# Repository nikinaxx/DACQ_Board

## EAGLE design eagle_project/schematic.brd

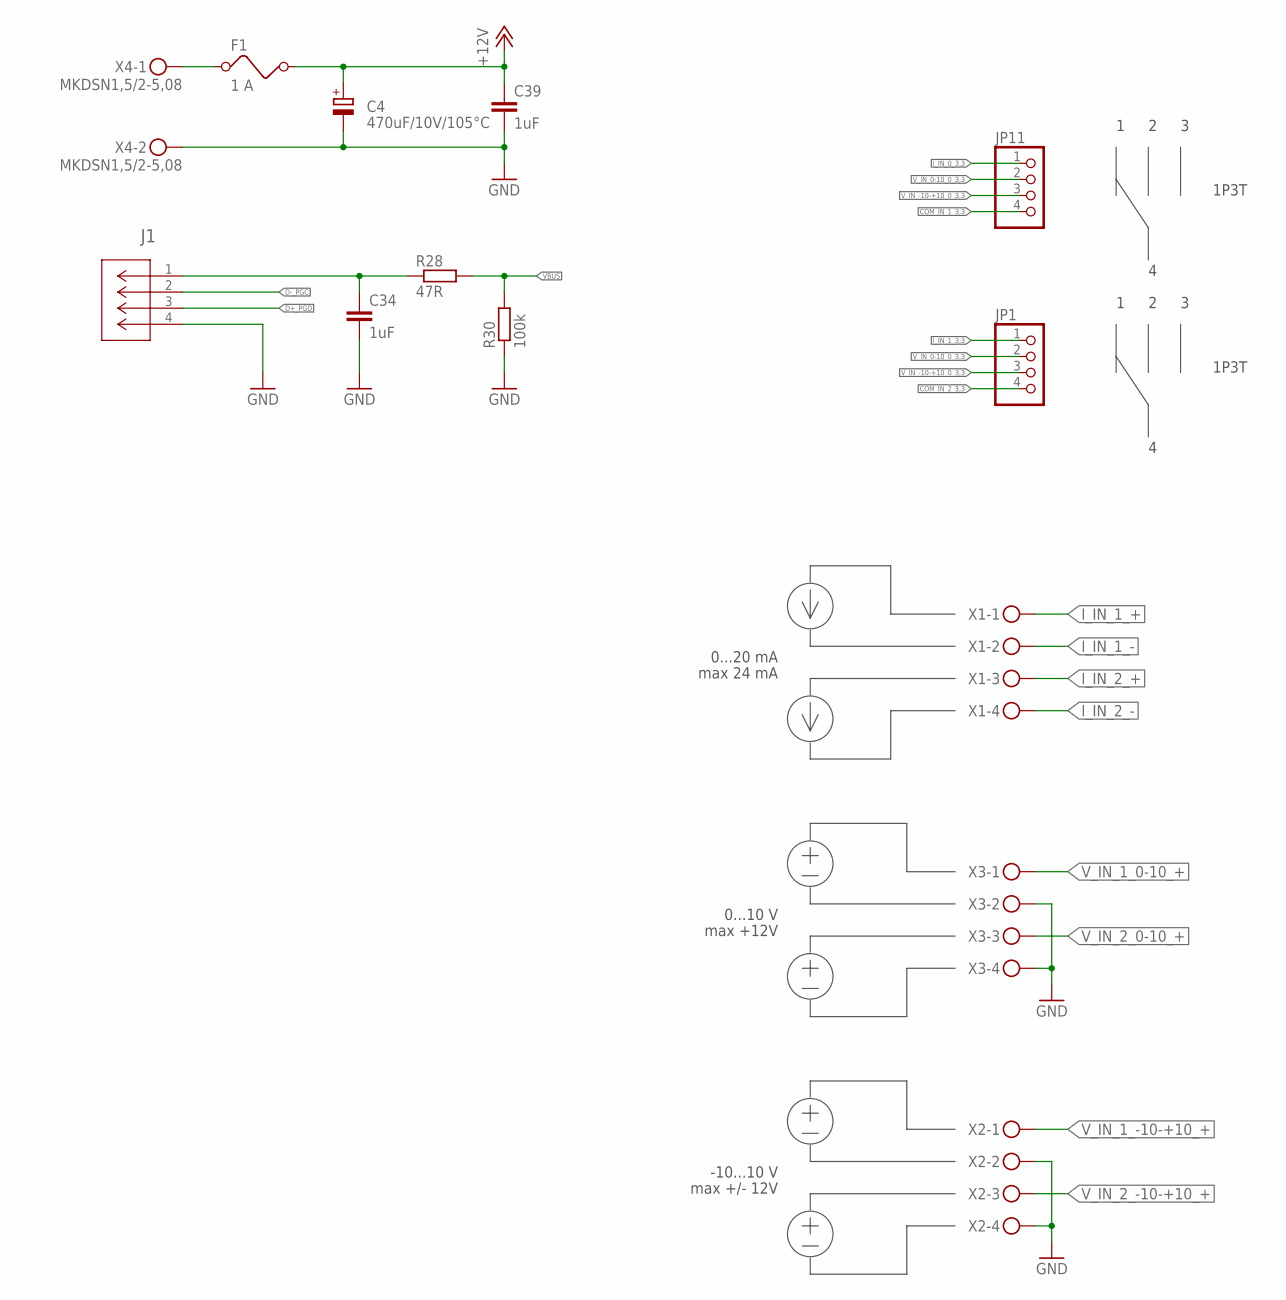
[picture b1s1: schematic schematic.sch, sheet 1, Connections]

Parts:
C4: 470uF/10V/105°C; E3,5-8
C34, C39: 1uF; C0805
F1: 1 A; FUSE
J1: USB-B; CONN_67068-8000_MOL
JP1, JP11: PINHD-1X4; 1X04
R28: 47R; M0805
R30: 100k; M0805
X1, X2, X3: MKDSN1,5/4-5,08
X4: MKDSN1,5/2-5,08

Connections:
+12V: C4.+, C39.1, F1.2; also elsewhere on the board
COM_IN_1_3,3: JP11.4
COM_IN_2_3,3: JP1.4
D+_PGD: J1.3; also elsewhere on the board
D-_PGC: J1.2; also elsewhere on the board
GND: C4.-, C34.2, C39.2, J1.4, R30.1, X2.2, X2.4, X3.2, X3.4, X4.2; also elsewhere on the board
I_IN_0_3,3: JP11.1; also elsewhere on the board
I_IN_1_3,3: JP1.1; also elsewhere on the board
I_IN_1_+: X1.1; also elsewhere on the board
I_IN_1_-: X1.2
I_IN_2_+: X1.3; also elsewhere on the board
I_IN_2_-: X1.4
unnamed: C34.1, J1.1, R28.1
unnamed: F1.1, X4.1
VBUS: R28.2, R30.2; also elsewhere on the board
V_IN_0-10_0_3,3: JP1.2, JP11.2; also elsewhere on the board
V_IN_1_0-10_+: X3.1; also elsewhere on the board
V_IN_1_-10-+10_+: X2.1; also elsewhere on the board
V_IN_2_0-10_+: X3.3; also elsewhere on the board
V_IN_2_-10-+10_+: X2.3; also elsewhere on the board
V_IN_-10-+10_0_3,3: JP1.3, JP11.3; also elsewhere on the board

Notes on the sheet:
max +12V
0...10 V
max 24 mA
0...20 mA
1P3T
max +/- 12V
-10...10 V

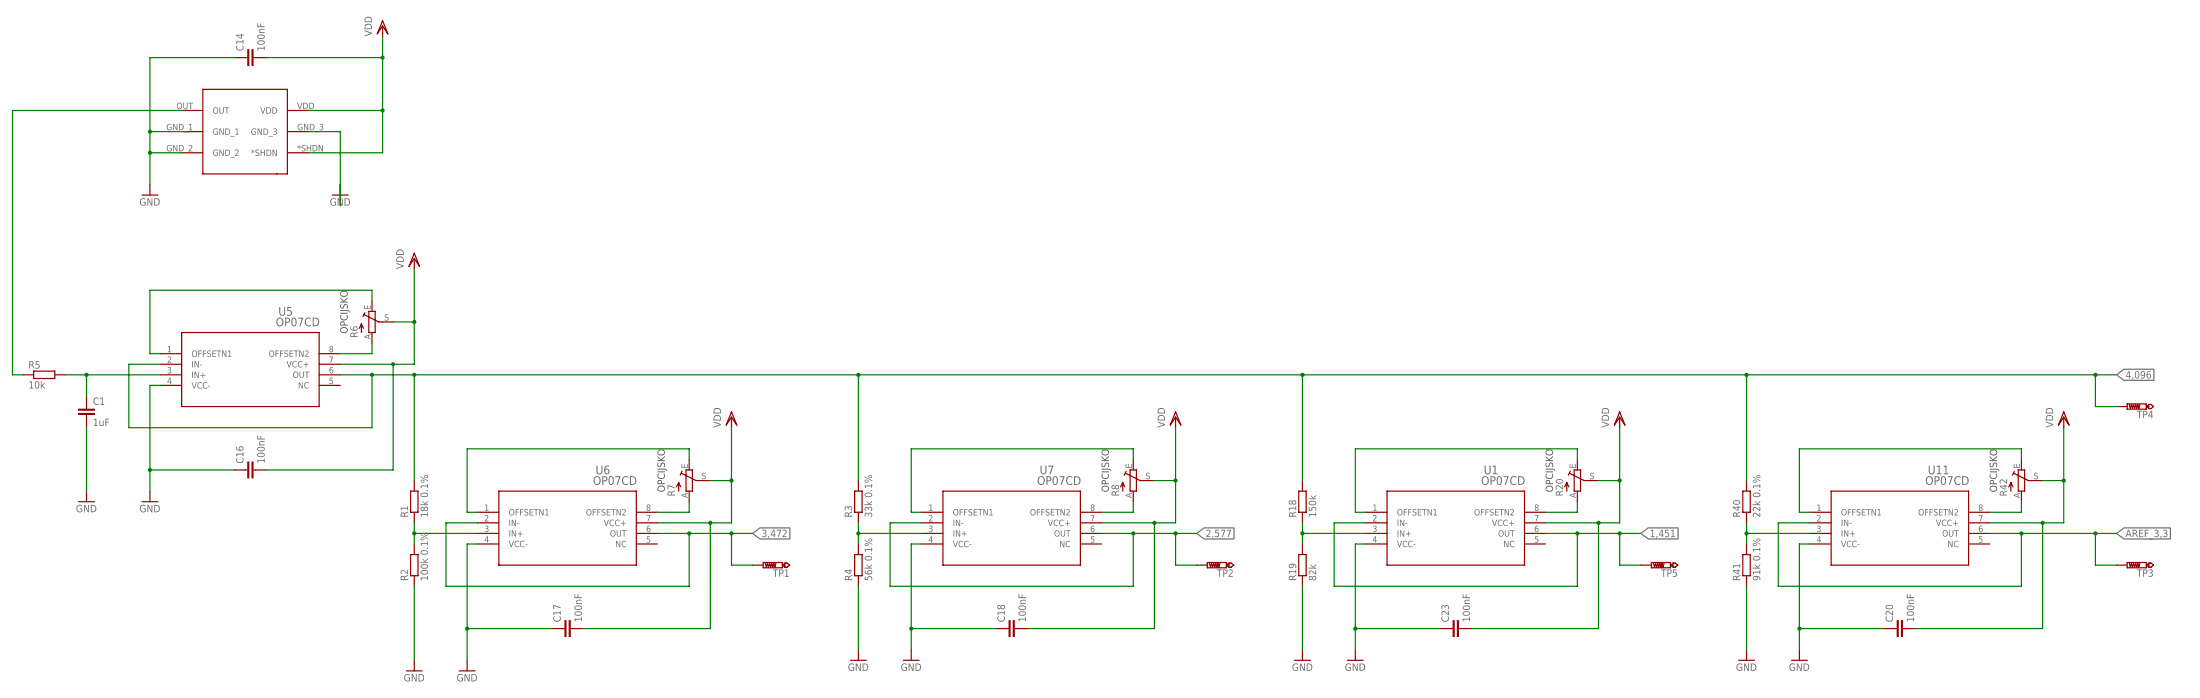
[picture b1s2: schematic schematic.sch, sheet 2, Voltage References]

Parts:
C1: 1uF; C0805
C14, C16, C17, C18, C20, C23: 100nF; C0805
R1: 18k 0.1%; R0805
R2: 100k 0.1%; R0805
R3: 33k 0.1%; R0805
R4: 56k 0.1%; R0805
R5: 10k; R0805
R6, R7, R8, R20, R42: TRIM_EU-S64W; S64W
R18: 150k; R0805
R19: 82k; R0805
R40: 22k 0.1%; R0805
R41: 91k 0.1%; R0805
TP1, TP2, TP3, TP4, TP5: PTR1PAD1-13; P1-13
U1, U5, U6, U7, U11: OP07CD; D8
U4: MCP1501T-40E/CHY; SOT26

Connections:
1,451: TP5.TP, U1.2 (IN-), U1.6 (OUT); also elsewhere on the board
2,577: TP2.TP, U7.2 (IN-), U7.6 (OUT); also elsewhere on the board
3,472: TP1.TP, U6.2 (IN-), U6.6 (OUT); also elsewhere on the board
4,096: R1.2, R3.2, R18.2, R40.2, TP4.TP, U5.2 (IN-), U5.6 (OUT); also elsewhere on the board
AREF_3,3: TP3.TP, U11.2 (IN-), U11.6 (OUT); also elsewhere on the board
GND: C1.2, C14.1, C16.1, C17.1, C18.1, C20.1, C23.1, R2.1, R4.1, R19.1, R41.1, U1.4 (VCC-), U4.GND_1, U4.GND_2, U4.GND_3, U5.4 (VCC-), U6.4 (VCC-), U7.4 (VCC-), U11.4 (VCC-); also elsewhere on the board
unnamed: R3.1, R4.2, U7.3 (IN+)
unnamed: R6.A, U5.8 (OFFSETN2)
unnamed: C1.1, R5.2, U5.3 (IN+)
unnamed: R6.E, U5.1 (OFFSETN1)
unnamed: R5.1, U4.OUT
unnamed: R1.1, R2.2, U6.3 (IN+)
unnamed: R7.A, U6.8 (OFFSETN2)
unnamed: R7.E, U6.1 (OFFSETN1)
unnamed: R8.A, U7.8 (OFFSETN2)
unnamed: R8.E, U7.1 (OFFSETN1)
unnamed: R18.1, R19.2, U1.3 (IN+)
unnamed: R20.A, U1.8 (OFFSETN2)
unnamed: R20.E, U1.1 (OFFSETN1)
unnamed: R40.1, R41.2, U11.3 (IN+)
unnamed: R42.A, U11.8 (OFFSETN2)
unnamed: R42.E, U11.1 (OFFSETN1)
VDD: C14.2, C16.2, C17.2, C18.2, C20.2, C23.2, R6.S, R7.S, R8.S, R20.S, R42.S, U1.7 (VCC+), U4.*SHDN, U4.VDD, U5.7 (VCC+), U6.7 (VCC+), U7.7 (VCC+), U11.7 (VCC+); also elsewhere on the board

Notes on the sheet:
OPCIJSKO

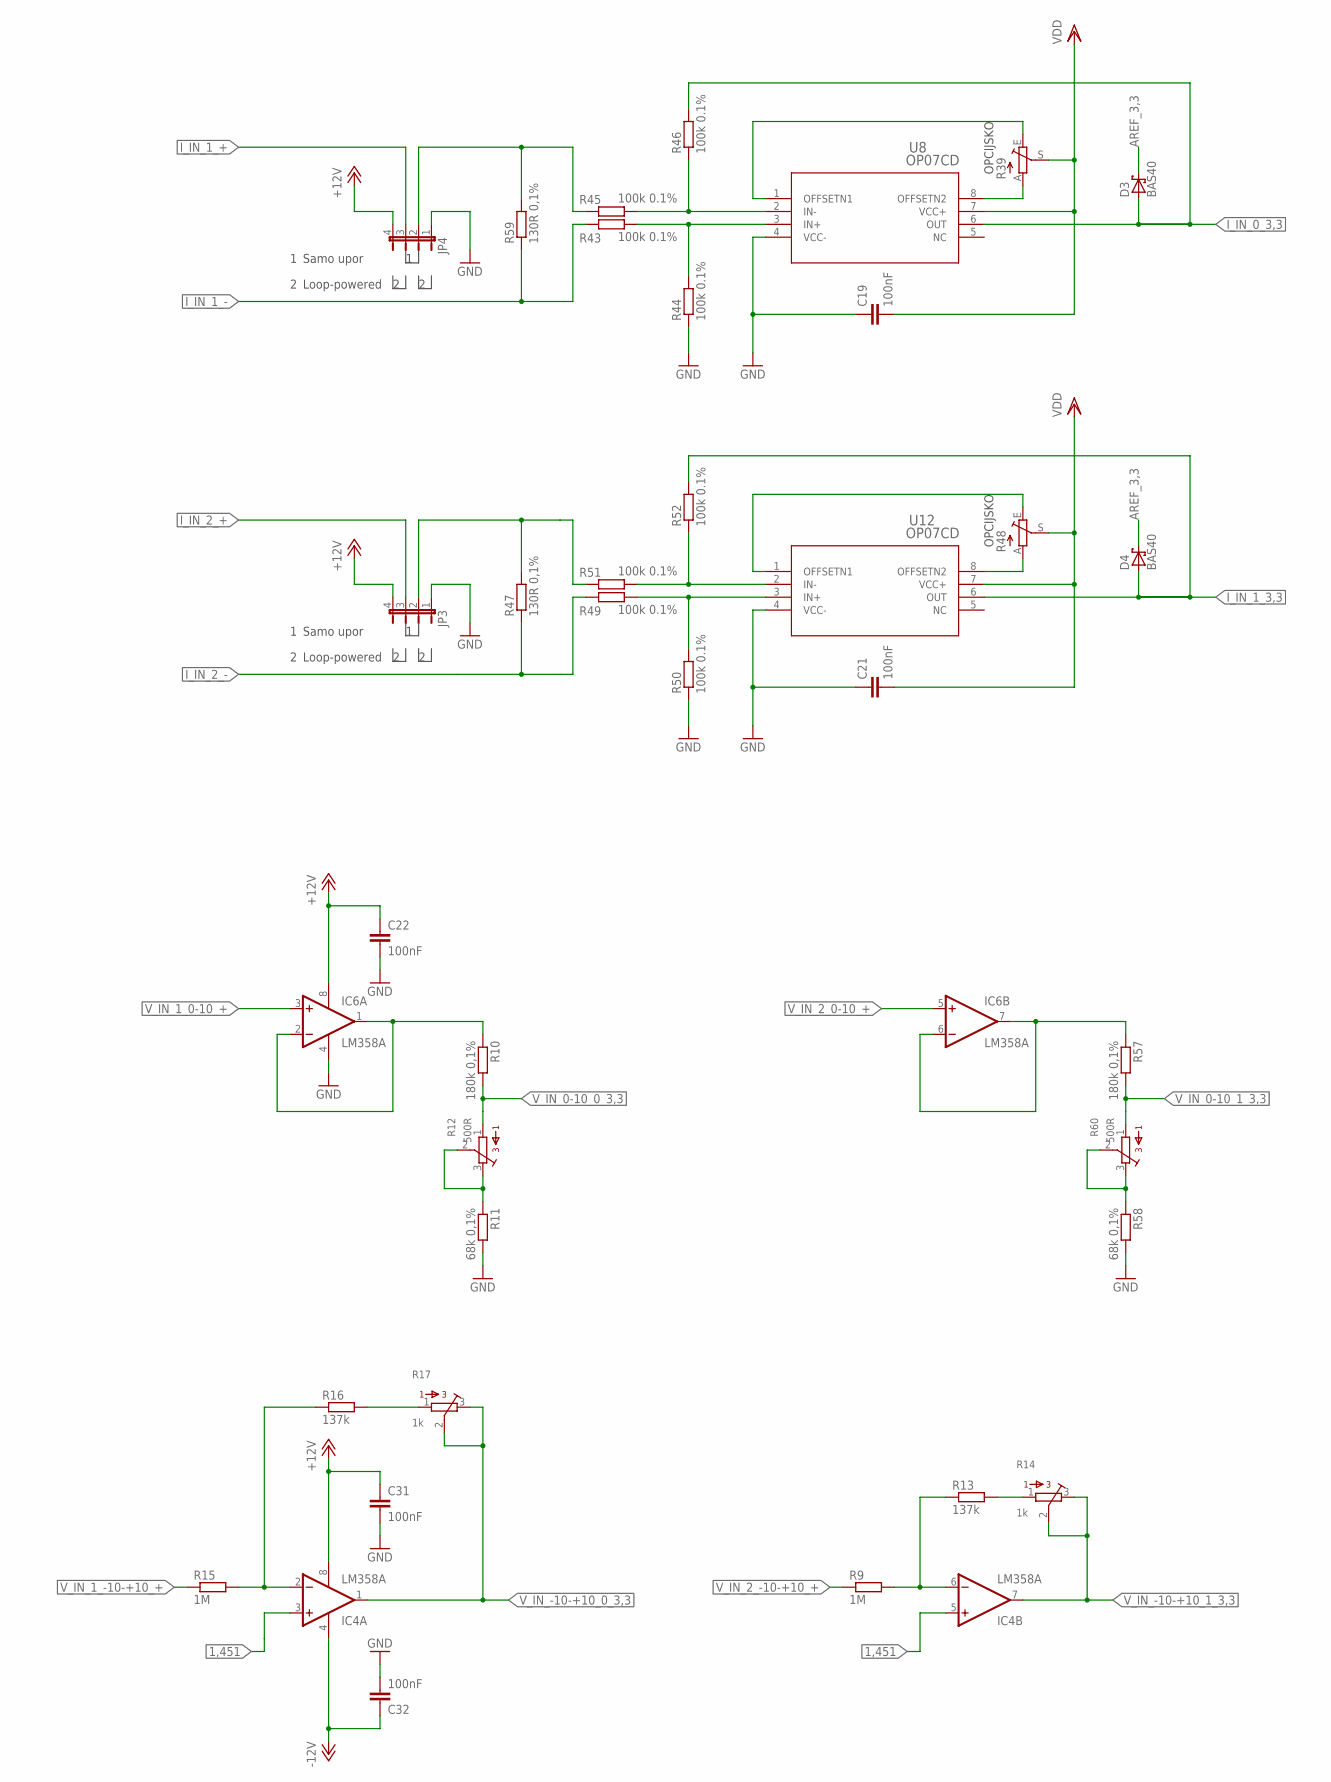
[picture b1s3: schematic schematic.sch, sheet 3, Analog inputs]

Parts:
C19, C21, C22, C31, C32: 100nF; C0805
D3, D4: BAS40; SOT23
IC4, IC6: LM358A; SO08
JP3, JP4: JP4E; JP4
R9, R15: 1M; R0805
R10, R57: 180k 0,1%; R0805
R11, R58: 68k 0,1%; R0805
R12, R60: 500R; 3362P
R13, R16: 137k; R0805
R14, R17: 1k; 3362P
R39, R48: TRIM_EU-S64W; S64W
R43, R44, R45, R46, R49, R50, R51, R52: 100k 0.1%; R0805
R47, R59: 130R 0,1%; R0805
U8, U12: OP07CD; D8

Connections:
1,451: IC4.3 (+IN), IC4.5 (+IN); also elsewhere on the board
+12V: C22.1, C31.1, IC4.8 (V+), IC6.8 (V+), JP3.4, JP4.4; also elsewhere on the board
-12V: C32.1, IC4.4 (V-); also elsewhere on the board
AREF_3,3: D3.3 (C), D4.3 (C); also elsewhere on the board
GND: C19.1, C21.1, C22.2, C31.2, C32.2, IC6.4 (V-), JP3.1, JP4.1, R11.2, R44.1, R50.1, R58.2, U8.4 (VCC-), U12.4 (VCC-); also elsewhere on the board
I_IN_0_3,3: D3.1 (A), R46.2, U8.6 (OUT); also elsewhere on the board
I_IN_1_3,3: D4.1 (A), R52.2, U12.6 (OUT); also elsewhere on the board
I_IN_1_+: JP4.3; also elsewhere on the board
I_IN_2_+: JP3.3; also elsewhere on the board
unnamed: R16.2, R17.1
unnamed: IC4.2 (-IN), R15.2, R16.1
unnamed: IC6.1 (OUT), IC6.2 (-IN), R10.1
unnamed: R11.1, R12.2, R12.3
unnamed: IC4.6 (-IN), R9.2, R13.1
unnamed: R13.2, R14.1
unnamed: R39.A, U8.8 (OFFSETN2)
unnamed: R39.E, U8.1 (OFFSETN1)
unnamed: R45.1, R46.1, U8.2 (IN-)
unnamed: R43.2, R44.2, U8.3 (IN+)
unnamed: JP3.2, R47.2, R51.2
unnamed: R47.1, R49.1
unnamed: R48.A, U12.8 (OFFSETN2)
unnamed: R48.E, U12.1 (OFFSETN1)
unnamed: R51.1, R52.1, U12.2 (IN-)
unnamed: R49.2, R50.2, U12.3 (IN+)
unnamed: R58.1, R60.2, R60.3
unnamed: JP4.2, R45.2, R59.2
unnamed: IC6.6 (-IN), IC6.7 (OUT), R57.1
unnamed: R43.1, R59.1
VDD: C19.2, C21.2, R39.S, R48.S, U8.7 (VCC+), U12.7 (VCC+); also elsewhere on the board
V_IN_0-10_0_3,3: R10.2, R12.1; also elsewhere on the board
V_IN_0-10_1_3,3: R57.2, R60.1; also elsewhere on the board
V_IN_1_0-10_+: IC6.3 (+IN); also elsewhere on the board
V_IN_1_-10-+10_+: R15.1; also elsewhere on the board
V_IN_2_0-10_+: IC6.5 (+IN); also elsewhere on the board
V_IN_2_-10-+10_+: R9.1; also elsewhere on the board
V_IN_-10-+10_0_3,3: IC4.1 (OUT), R17.2, R17.3; also elsewhere on the board
V_IN_-10-+10_1_3,3: IC4.7 (OUT), R14.2, R14.3; also elsewhere on the board

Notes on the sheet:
Samo upor
Loop-powered
OPCIJSKO

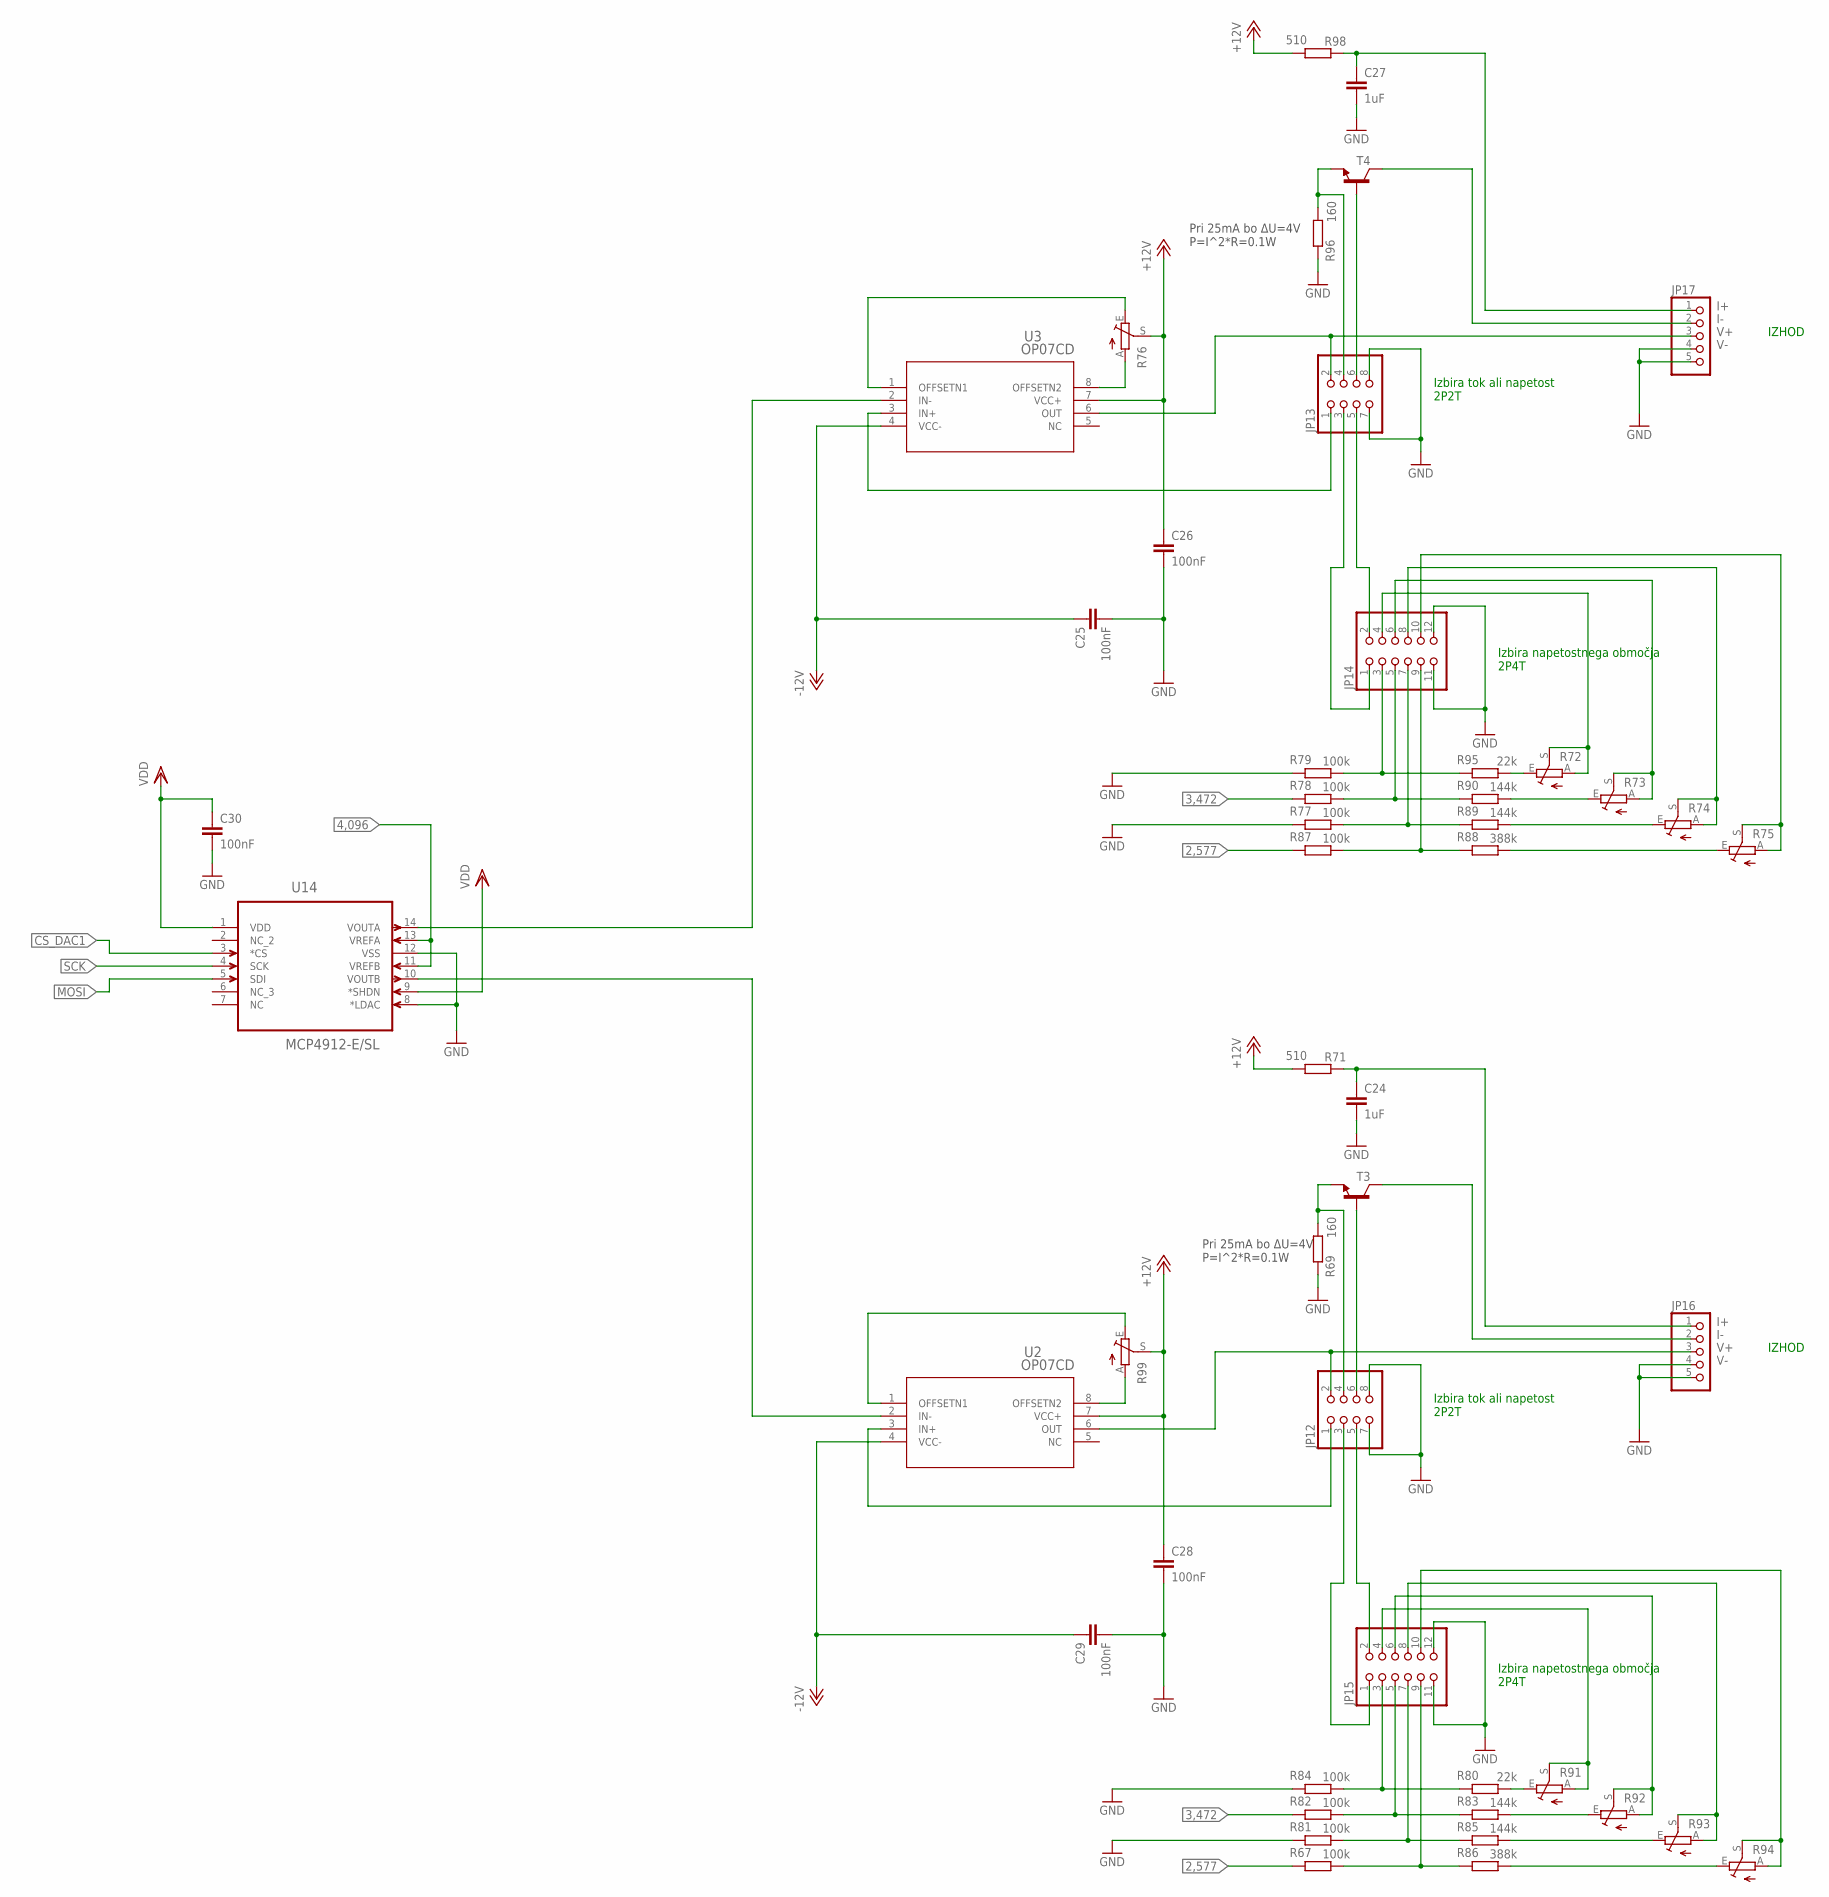
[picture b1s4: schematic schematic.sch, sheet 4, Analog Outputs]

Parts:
C24, C27: 1uF; C0805
C25, C26, C28, C29, C30: 100nF; C0805
JP12, JP13: PINHD-2X4; 2X04
JP14, JP15: PINHD-2X6; 2X06
JP16, JP17: PINHD-1X5; 1X05
R67, R77, R78, R79, R81, R82, R84, R87: 100k; R0805
R69, R96: 160; R0805
R71, R98: 510; R0805
R72, R73, R74, R75, R76, R91, R92, R93, R94, R99: TRIM_EU-S64W; S64W
R80, R95: 22k; R0805
R83, R85, R89, R90: 144k; R0805
R86, R88: 388k; R0805
T3, T4: MMBT3904LT1-NPN-SOT23-BEC; SOT23-BEC
U2, U3: OP07CD; D8
U14: MCP4912-E/SL; SOIC127P600X175-16N

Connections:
2,577: R67.2, R87.2; also elsewhere on the board
3,472: R78.2, R82.2; also elsewhere on the board
4,096: U14.11 (VREFB), U14.13 (VREFA); also elsewhere on the board
+12V: C26.1, C28.1, R71.1, R76.S, R98.1, R99.S, U2.7 (VCC+), U3.7 (VCC+); also elsewhere on the board
-12V: C25.1, C29.1, U2.4 (VCC-), U3.4 (VCC-); also elsewhere on the board
CS_DAC1: U14.3 (*CS); also elsewhere on the board
GND: C24.2, C25.2, C26.2, C27.2, C28.2, C29.2, C30.2, JP12.7, JP12.8, JP13.7, JP13.8, JP14.11, JP14.12, JP15.11, JP15.12, R69.2, R77.2, R79.2, R81.2, R84.2, R96.2, U14.8 (*LDAC), U14.12 (VSS); also elsewhere on the board
I+: C24.1, C27.1, JP16.1, JP17.1, R71.2, R98.2
I-: JP16.2, JP17.2, T3.C, T4.C
MOSI: U14.5 (SDI); also elsewhere on the board
unnamed: R99.A, U2.8 (OFFSETN2)
unnamed: U2.2 (IN-), U14.10 (VOUTB)
unnamed: JP13.4, R96.1, T4.E
unnamed: JP14.3, R79.1, R95.2
unnamed: JP14.7, R77.1, R89.2
unnamed: JP14.9, R87.1, R88.2
unnamed: JP14.5, R78.1, R90.2
unnamed: JP13.1, U3.3 (IN+)
unnamed: JP13.3, JP14.1
unnamed: JP13.5, JP14.2
unnamed: JP13.6, T4.B
unnamed: R72.E, R95.1
unnamed: JP14.6, R73.A, R73.S
unnamed: JP14.4, R72.A, R72.S
unnamed: JP12.4, R69.1, T3.E
unnamed: JP15.3, R80.2, R84.1
unnamed: JP15.7, R81.1, R85.2
unnamed: JP15.9, R67.1, R86.2
unnamed: JP15.5, R82.1, R83.2
unnamed: JP12.1, U2.3 (IN+)
unnamed: JP12.3, JP15.1
unnamed: JP12.5, JP15.2
unnamed: JP12.6, T3.B
unnamed: R80.1, R91.E
unnamed: JP15.6, R92.A, R92.S
unnamed: JP15.4, R91.A, R91.S
unnamed: JP15.8, R93.A, R93.S
unnamed: JP15.10, R94.A, R94.S
unnamed: R83.1, R92.E
unnamed: R85.1, R93.E
unnamed: R86.1, R94.E
unnamed: JP14.8, R74.A, R74.S
unnamed: JP14.10, R75.A, R75.S
unnamed: R73.E, R90.1
unnamed: R74.E, R89.1
unnamed: R99.E, U2.1 (OFFSETN1)
unnamed: R75.E, R88.1
unnamed: R76.A, U3.8 (OFFSETN2)
unnamed: R76.E, U3.1 (OFFSETN1)
SCK: U14.4 (SCK); also elsewhere on the board
V+: JP12.2, JP13.2, JP16.3, JP17.3, U2.6 (OUT), U3.6 (OUT)
V-: JP16.4, JP16.5, JP17.4, JP17.5
VDD: C30.1, U14.1 (VDD), U14.9 (*SHDN); also elsewhere on the board

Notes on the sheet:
Pri 25mA bo ΔU=4V P=I^2*R=0.1W
Izbira tok ali napetost 2P2T
IZHOD
Izbira napetostnega območja 2P4T

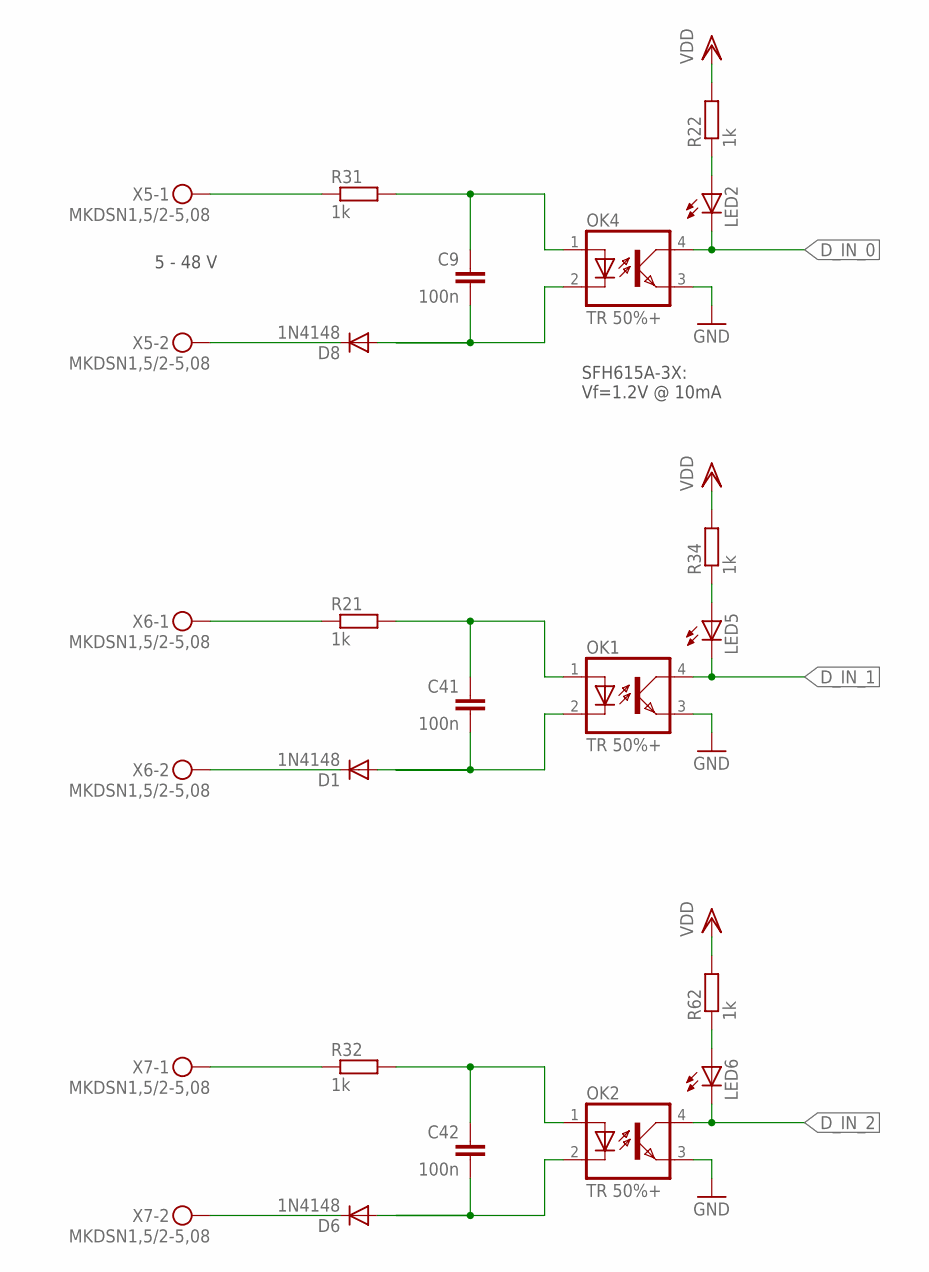
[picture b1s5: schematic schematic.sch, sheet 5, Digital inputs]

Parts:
C9, C41, C42: 100n; C0805
D1, D6, D8: 1N4148; MINIMELF
LED2, LED5, LED6: LEDCHIPLED_0805; CHIPLED_0805
OK1, OK2, OK4: TR 50%+; DIL04
R21, R31, R32: 1k; R2512
R22, R34, R62: 1k; R0805
X5, X6, X7: MKDSN1,5/2-5,08

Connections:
+5V: R22.2, R34.2, R62.2; also elsewhere on the board
D_IN_0: LED2.C, OK4.4 (COL); also elsewhere on the board
D_IN_1: LED5.C, OK1.4 (COL); also elsewhere on the board
D_IN_2: LED6.C, OK2.4 (COL); also elsewhere on the board
GND: OK1.3 (EMIT), OK2.3 (EMIT), OK4.3 (EMIT); also elsewhere on the board
unnamed: R21.1, X6.1
unnamed: LED2.A, R22.1
unnamed: C41.1, OK1.1 (A), R21.2
unnamed: C41.2, D1.A, OK1.2 (C)
unnamed: D1.C, X6.2
unnamed: LED5.A, R34.1
unnamed: R31.1, X5.1
unnamed: C9.2, D8.A, OK4.2 (C)
unnamed: R32.1, X7.1
unnamed: LED6.A, R62.1
unnamed: C42.1, OK2.1 (A), R32.2
unnamed: C42.2, D6.A, OK2.2 (C)
unnamed: D6.C, X7.2
unnamed: C9.1, OK4.1 (A), R31.2
unnamed: D8.C, X5.2

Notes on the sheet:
SFH615A-3X: Vf=1.2V @ 10mA
5 - 48 V

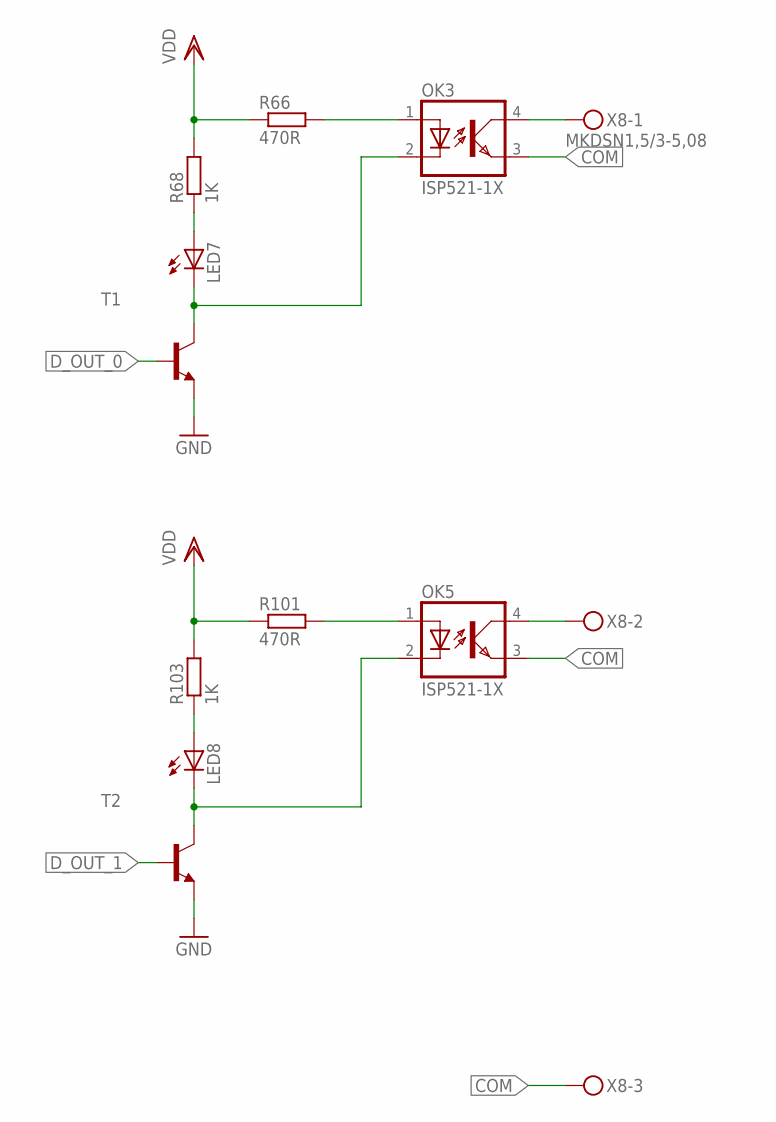
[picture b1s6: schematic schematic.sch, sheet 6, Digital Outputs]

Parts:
LED7, LED8: LEDCHIPLED_0805; CHIPLED_0805
OK3, OK5: ISP521-1X; DIL04
R66, R101: 470R; R0805
R68, R103: 1K; R0805
T1, T2: MMBT3904LT1-NPN-SOT23-BEC; SOT23-BEC
X8: MKDSN1,5/3-5,08

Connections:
COM: OK3.3 (EMIT), OK5.3 (EMIT), X8.3
D_OUT_0: T1.B; also elsewhere on the board
D_OUT_1: T2.B; also elsewhere on the board
GND: T1.E, T2.E; also elsewhere on the board
unnamed: OK3.1 (A), R66.2
unnamed: OK3.4 (COL), X8.1
unnamed: LED7.A, R68.1
unnamed: LED7.C, OK3.2 (C), T1.C
unnamed: OK5.1 (A), R101.2
unnamed: OK5.4 (COL), X8.2
unnamed: LED8.A, R103.1
unnamed: LED8.C, OK5.2 (C), T2.C
VCC: R66.1, R68.2, R101.1, R103.2

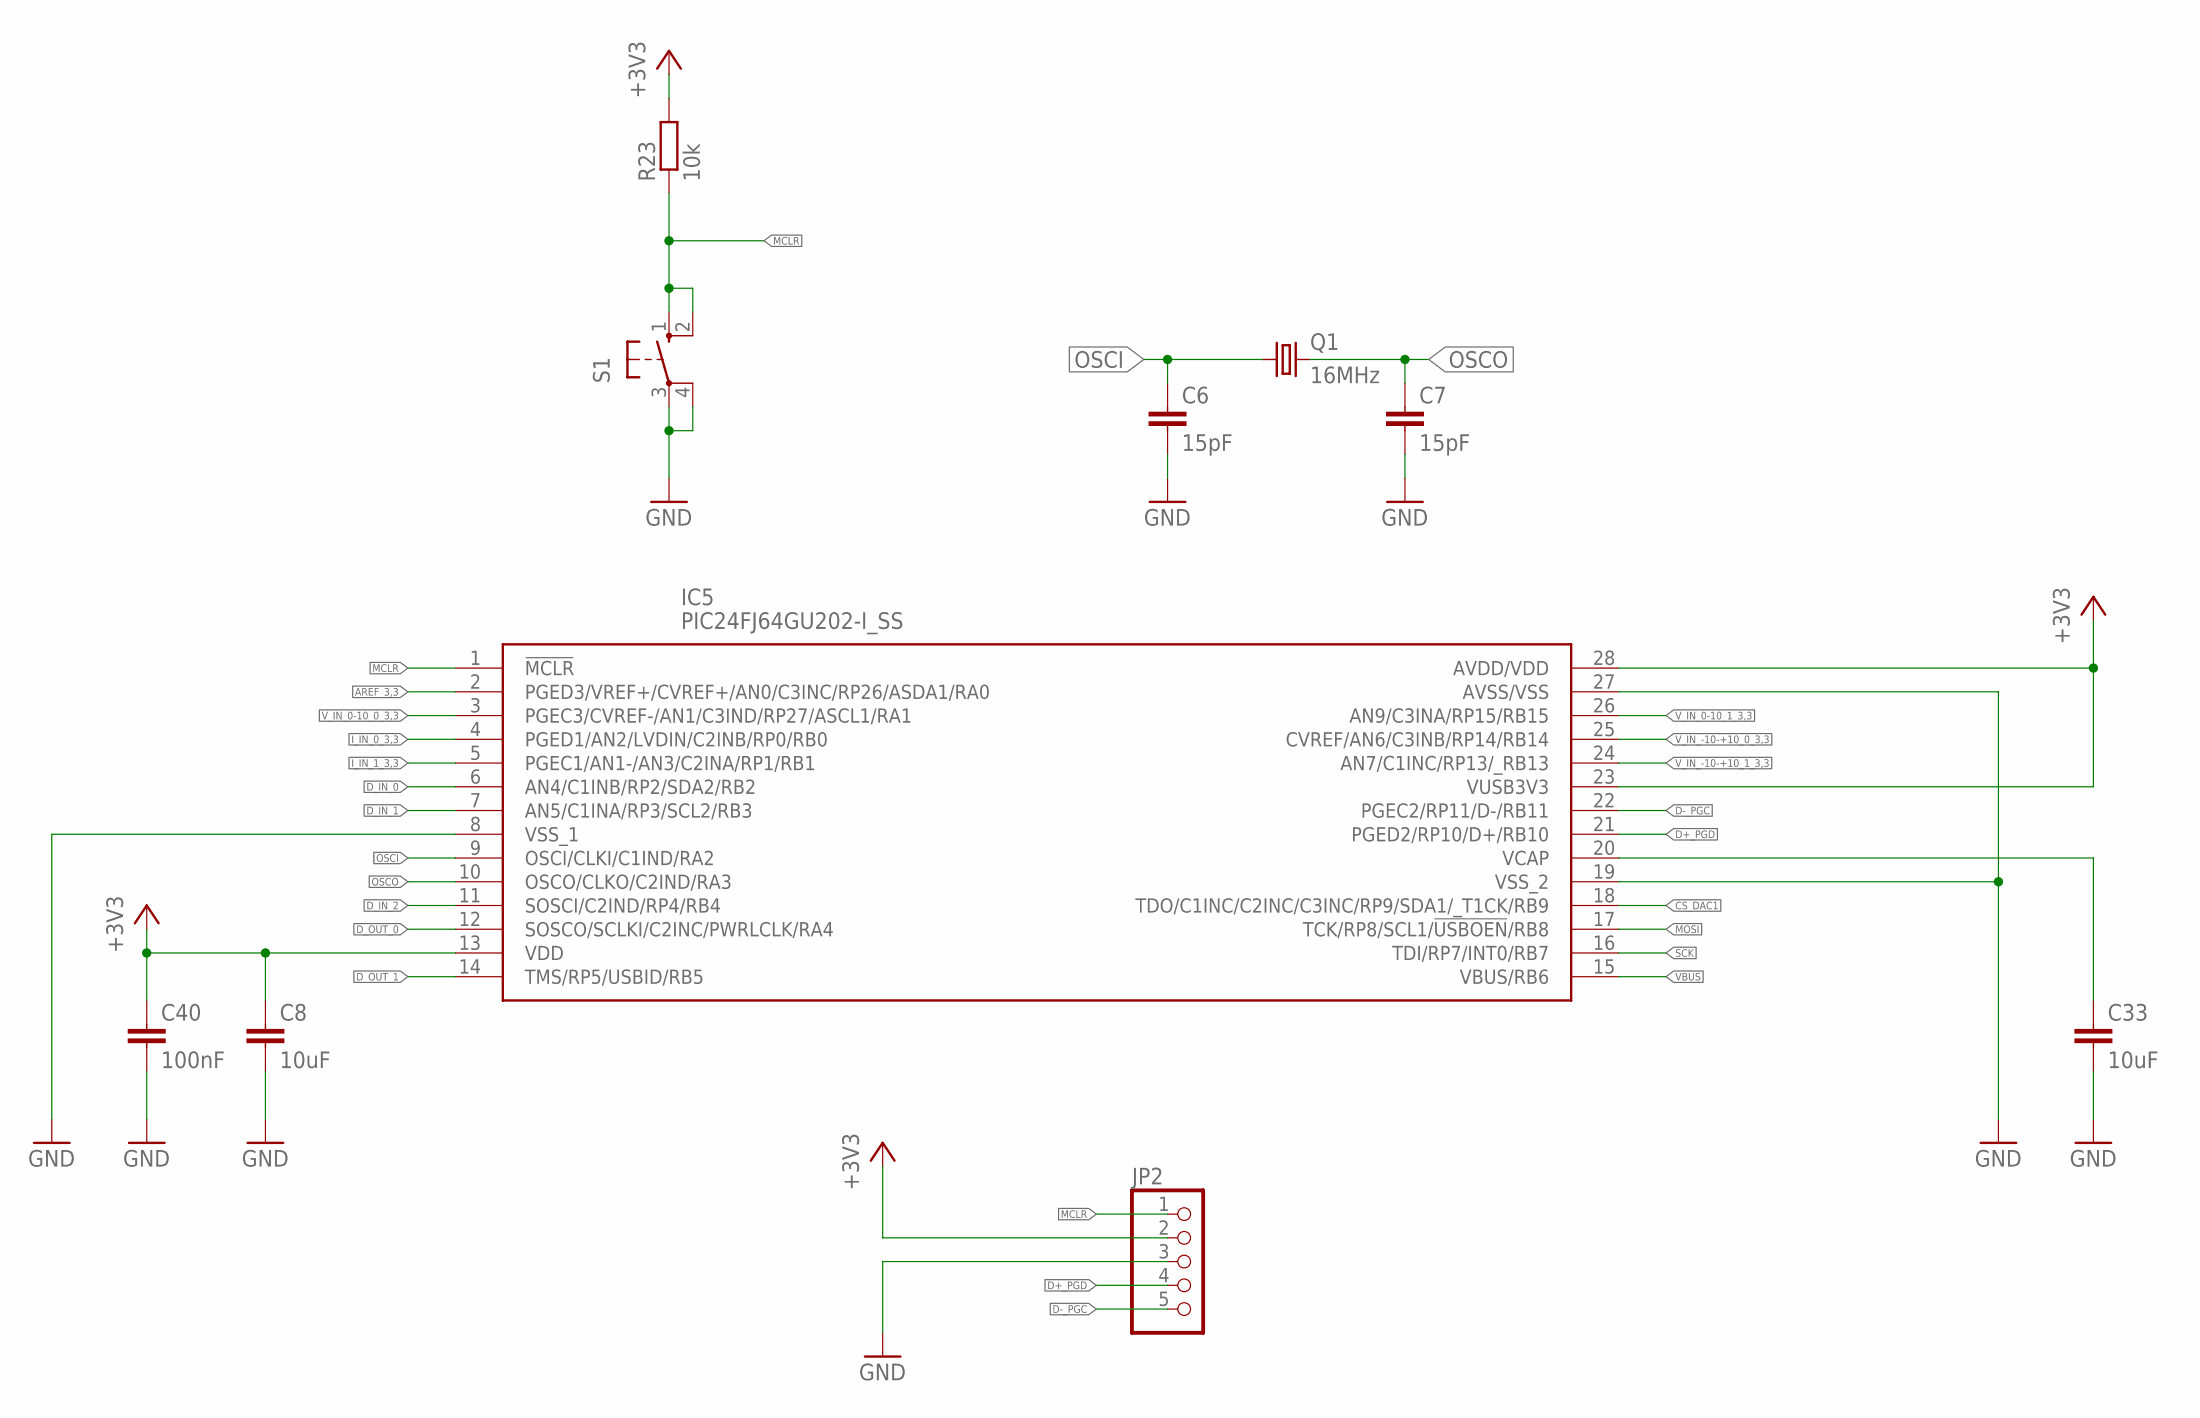
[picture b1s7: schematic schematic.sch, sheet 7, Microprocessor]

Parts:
C6, C7: 15pF; C0805
C8, C33: 10uF; C0805
C40: 100nF; C0805
IC5: PIC24FJ64GU202-I_SS; SOP65P780X200-28N
JP2: PINHD-1X5; 1X05
Q1: 16MHz; HC49U-V
R23: 10k; R0805
S1: 10-XX; B3F-10XX

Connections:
+3V3: C8.1, C40.1, IC5.13 (VDD), IC5.23 (VUSB3V3), IC5.28 (AVDD/VDD), JP2.2, R23.2; also elsewhere on the board
AREF_3,3: IC5.2 (PGED3/VREF+/CVREF+/AN0/C3INC/RP26/ASDA1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); also elsewhere on the board
CS_DAC1: IC5.18 (TDO/C1INC/C2INC/C3INC/RP9/SDA1/_T1CK/RB9); also elsewhere on the board
D+_PGD: IC5.21 (PGED2/RP10/D+/RB10), JP2.4; also elsewhere on the board
D-_PGC: IC5.22 (PGEC2/RP11/D-/RB11), JP2.5; also elsewhere on the board
D_IN_0: IC5.6 (AN4/C1INB/RP2/SDA2/RB2); also elsewhere on the board
D_IN_1: IC5.7 (AN5/C1INA/RP3/SCL2/RB3); also elsewhere on the board
D_IN_2: IC5.11 (SOSCI/C2IND/RP4/RB4); also elsewhere on the board
D_OUT_0: IC5.12 (SOSCO/SCLKI/C2INC/PWRLCLK/RA4); also elsewhere on the board
D_OUT_1: IC5.14 (TMS/RP5/USBID/RB5); also elsewhere on the board
GND: C6.2, C7.2, C8.2, C33.2, C40.2, IC5.8 (VSS_1), IC5.19 (VSS_2), IC5.27 (AVSS/VSS), JP2.3, S1.3, S1.4 (P1); also elsewhere on the board
I_IN_0_3,3: IC5.4 (PGED1/AN2/LVDIN/C2INB/RP0/RB0); also elsewhere on the board
I_IN_1_3,3: IC5.5 (PGEC1/AN1-/AN3/C2INA/RP1/RB1); also elsewhere on the board
MCLR: IC5.1 (!MCLR), JP2.1, R23.1, S1.1 (S), S1.2 (S1)
MOSI: IC5.17 (TCK/RP8/SCL1/!USBOEN!/RB8); also elsewhere on the board
unnamed: C33.1, IC5.20 (VCAP)
OSCI: C6.1, IC5.9 (OSCI/CLKI/C1IND/RA2), Q1.1
OSCO: C7.1, IC5.10 (OSCO/CLKO/C2IND/RA3), Q1.2
SCK: IC5.16 (TDI/RP7/INT0/RB7); also elsewhere on the board
VBUS: IC5.15 (VBUS/RB6); also elsewhere on the board
V_IN_0-10_0_3,3: IC5.3 (PGEC3/CVREF-/AN1/C3IND/RP27/ASCL1/RA1); also elsewhere on the board
V_IN_0-10_1_3,3: IC5.26 (AN9/C3INA/RP15/RB15); also elsewhere on the board
V_IN_-10-+10_0_3,3: IC5.25 (CVREF/AN6/C3INB/RP14/RB14); also elsewhere on the board
V_IN_-10-+10_1_3,3: IC5.24 (AN7/C1INC/RP13/_RB13); also elsewhere on the board

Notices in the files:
DACQ_Board.X/mcc_generated_files/pin_manager.h:
(c) 2020 Microchip Technology Inc. and its subsidiaries. You may use this
parts and their libraries:
COPYRIGHT: Copyright (C) 2022 Ultra Librarian. All rights reserved.
